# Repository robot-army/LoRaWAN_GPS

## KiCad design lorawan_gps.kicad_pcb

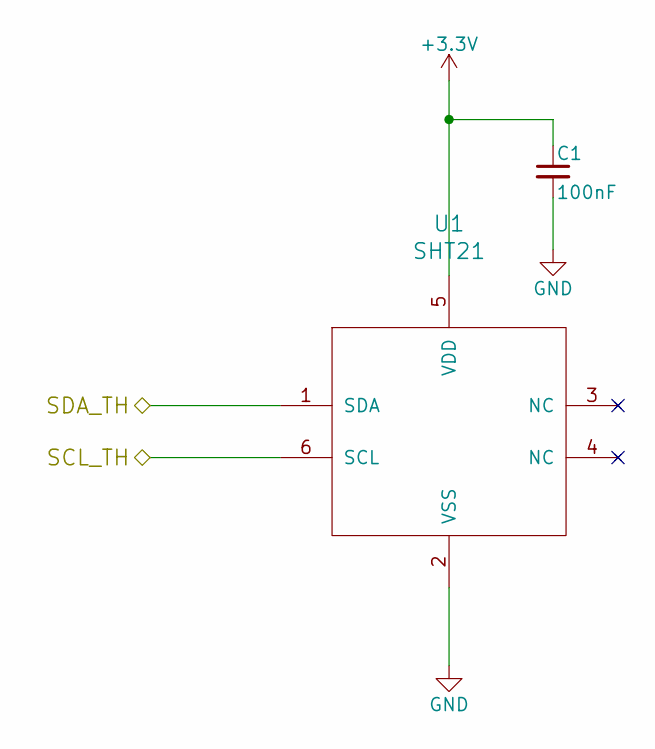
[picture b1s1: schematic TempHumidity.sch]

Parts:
C1: 100nF; C_0603
U1: SHT21

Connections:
/MCU/MPU_SCL: U1.6 (SCL); also elsewhere on the board
/MCU/MPU_SDA: U1.1 (SDA); also elsewhere on the board
GND: C1.2, U1.2 (VSS); also elsewhere on the board

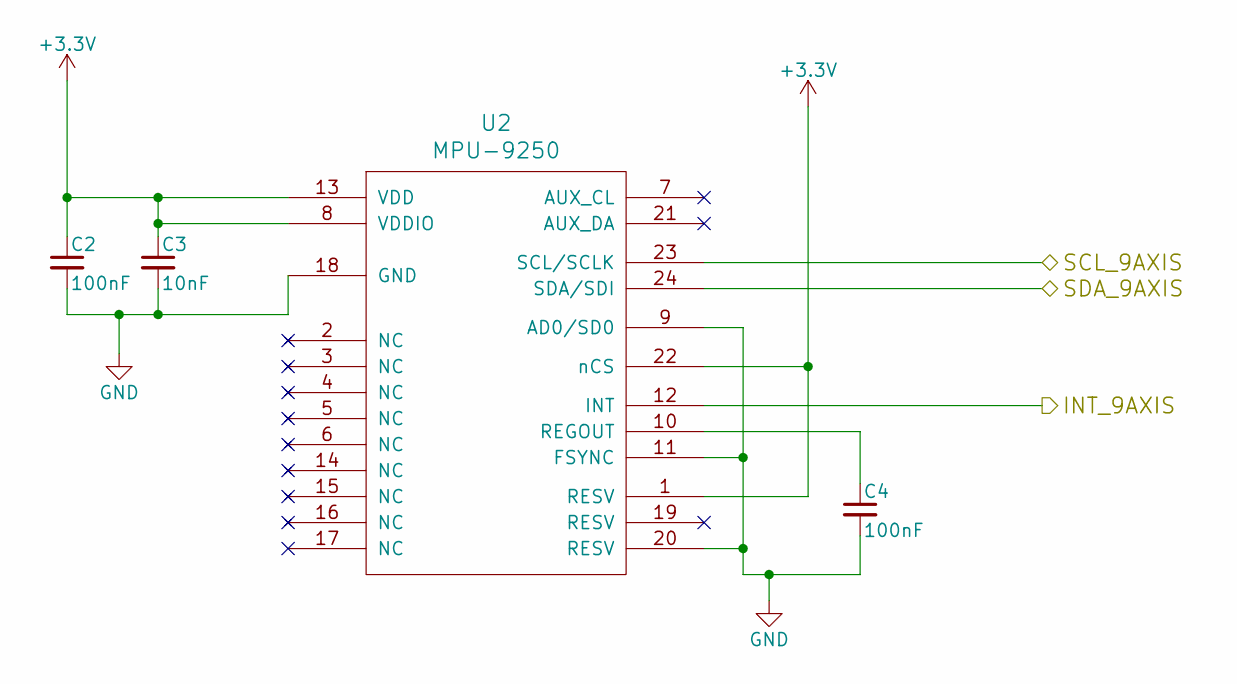
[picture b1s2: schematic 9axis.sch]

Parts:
C2, C4: 100nF; C_0603
C3: 10nF; C_0603
U2: MPU-9250; QFN-24-1EP_3x3mm_Pitch0.4mm

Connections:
/9axis/INT_9AXIS: U2.12 (INT); also elsewhere on the board
/MCU/MPU_SCL: U2.23 (SCL/SCLK); also elsewhere on the board
/MCU/MPU_SDA: U2.24 (SDA/SDI); also elsewhere on the board
GND: C2.2, C3.2, C4.2, U2.9 (AD0/SD0), U2.11 (FSYNC), U2.18 (GND), U2.20 (RESV); also elsewhere on the board
unnamed: C4.1, U2.10 (REGOUT)

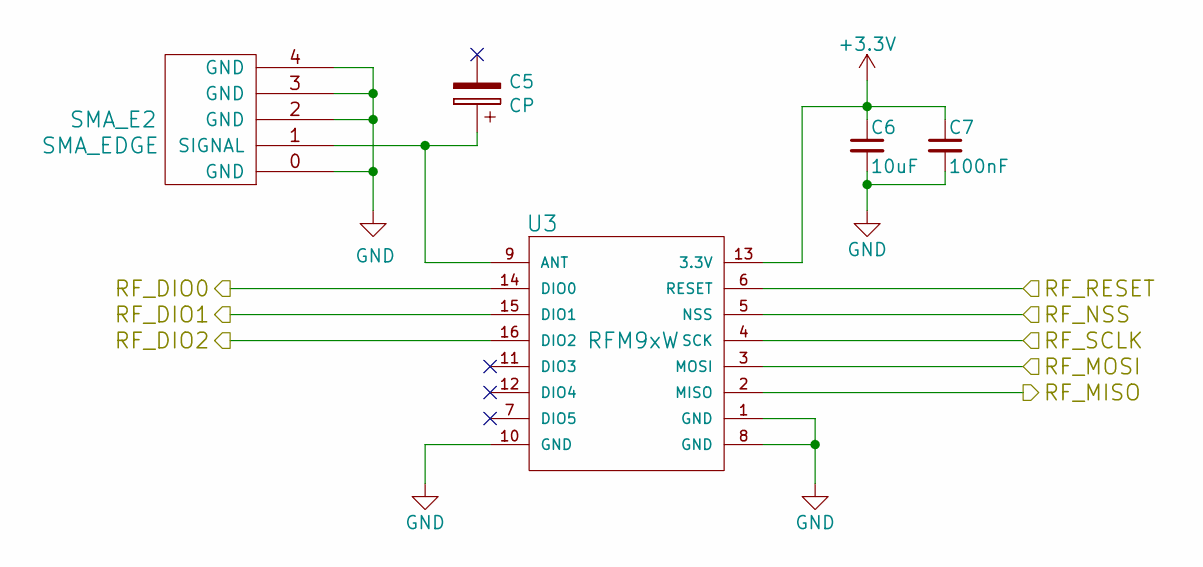
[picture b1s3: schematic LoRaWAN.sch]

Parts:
C5: CP; 0868AT43A0020; MFG Part Number 0868AT43A0020
C6: 10uF; C_0805
C7: 100nF; C_0603
SMA_E2: SMA_EDGE
U3: RFM9xW

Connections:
/MCU/MPU_D14: U3.6 (RESET); also elsewhere on the board
/MCU/MPU_IN14: U3.15 (DIO1); also elsewhere on the board
/MCU/MPU_INT5: U3.16 (DIO2); also elsewhere on the board
/MCU/MPU_INT9: U3.14 (DIO0); also elsewhere on the board
/MCU/MPU_MISO: U3.2 (MISO); also elsewhere on the board
/MCU/MPU_MOSI: U3.3 (MOSI); also elsewhere on the board
/MCU/MPU_SCK: U3.4 (SCK); also elsewhere on the board
/MCU/MPU_SS: U3.5 (NSS); also elsewhere on the board
GND: C6.2, C7.2, SMA_E2.0 (GND), SMA_E2.2 (GND), SMA_E2.3 (GND), SMA_E2.4 (GND), U3.1 (GND), U3.8 (GND), U3.10 (GND); also elsewhere on the board
unnamed: C5.1, SMA_E2.1 (SIGNAL), U3.9 (ANT)

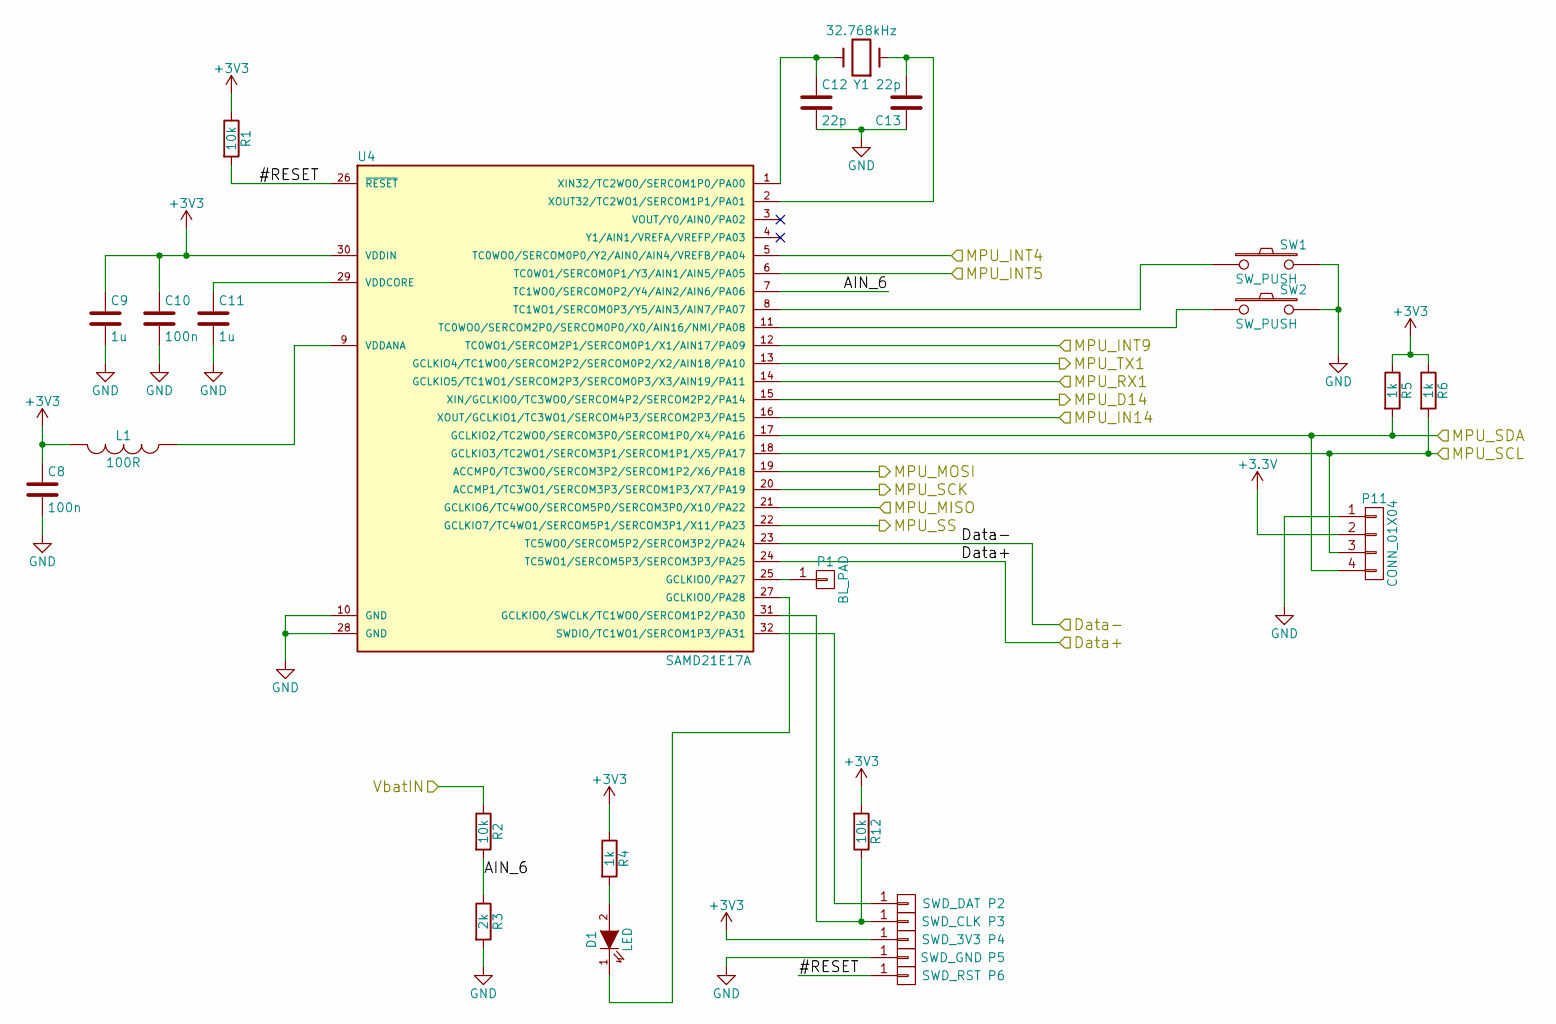
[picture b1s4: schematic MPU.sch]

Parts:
C8, C10: 100n; C_0603
C9, C11: 1u; C_0603
C12, C13: 22p; C_0603
D1: LED; C_0603
L1: 100R; C_0603
P1: BL_PAD; Measurement_Point_Round-TH_Small
P2: SWD_DAT; Measurement_Point_Round-TH_Small
P3: SWD_CLK; Measurement_Point_Round-TH_Small
P4: SWD_3V3; Measurement_Point_Round-TH_Small
P5: SWD_GND; Measurement_Point_Round-TH_Small
P6: SWD_RST; Measurement_Point_Round-TH_Small
P11: CONN_01X04; Pin_Header_Straight_1x04
R1, R2, R12: 10k; C_0603
R3: 2k; C_0603
R4, R5, R6: 1k; C_0603
SW1, SW2: SW_PUSH; SW_SPST_EVQP2
U4: SAMD21E17A; QFN-32-1EP_5x5mm_Pitch0.5mm
Y1: 32.768kHz; ABS07

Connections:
/9axis/INT_9AXIS: U4.5 (TC0WO0/SERCOM0P0/Y2/AIN0/AIN4/VREFB/PA04); also elsewhere on the board
/Battery and USB Connector/D+: U4.24 (TC5WO1/SERCOM5P3/SERCOM3P3/PA25); also elsewhere on the board
/Battery and USB Connector/D-: U4.23 (TC5WO0/SERCOM5P2/SERCOM3P2/PA24); also elsewhere on the board
/Battery and USB Connector/V_BAT: R2.1; also elsewhere on the board
/Battery and USB Connector/V_USB_Sense: U4.3 (VOUT/Y0/AIN0/PA02); also elsewhere on the board
/MCU/#RESET: P6.1, R1.2, U4.26 (~RESET~)
/MCU/AIN_6: R2.2, R3.1, U4.7 (TC1WO0/SERCOM0P2/Y4/AIN2/AIN6/PA06)
/MCU/MPU_D14: U4.15 (XIN/GCLKIO0/TC3WO0/SERCOM4P2/SERCOM2P2/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); also elsewhere on the board
/MCU/MPU_IN14: U4.16 (XOUT/GCLKIO1/TC3WO1/SERCOM4P3/SERCOM2P3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); also elsewhere on the board
/MCU/MPU_INT5: U4.6 (TC0W01/SERCOM0P1/Y3/AIN1/AIN5/PA05); also elsewhere on the board
/MCU/MPU_INT9: U4.12 (TC0WO1/SERCOM2P1/SERCOM0P1/X1/AIN17/PA09); also elsewhere on the board
/MCU/MPU_MISO: U4.21 (GCLKIO6/TC4WO0/SERCOM5P0/SERCOM3P0/X10/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); also elsewhere on the board
/MCU/MPU_MOSI: U4.19 (ACCMP0/TC3WO0/SERCOM3P2/SERCOM1P2/X6/PA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); also elsewhere on the board
/MCU/MPU_RX1: U4.14 (GCLKIO5/TC1WO1/SERCOM2P3/SERCOM0P3/X3/A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); also elsewhere on the board
/MCU/MPU_SCK: U4.20 (ACCMP1/TC3WO1/SERCOM3P3/SERCOM1P3/X7/PA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); also elsewhere on the board
/MCU/MPU_SCL: P11.3, R6.2, U4.18 (GCLKIO3/TC2WO1/SERCOM3P1/SERCOM1P1/X5/P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); also elsewhere on the board
/MCU/MPU_SDA: P11.4, R5.2, U4.17 (GCLKIO2/TC2WO0/SERCOM3P0/SERCOM1P0/X4/P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); also elsewhere on the board
/MCU/MPU_SS: U4.22 (GCLKIO7/TC4WO1/SERCOM5P1/SERCOM3P1/X11/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); also elsewhere on the board
/MCU/MPU_TX1: U4.13 (GCLKIO4/TC1WO0/SERCOM2P2/SERCOM0P2/X2/A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); also elsewhere on the board
GND: C8.2, C9.2, C10.2, C11.2, C12.2, C13.1, P5.1, P11.1, R3.2, SW1.2, SW2.2, U4.10 (GND), U4.28 (GND); also elsewhere on the board
unnamed: C11.1, U4.29 (VDDCORE)
unnamed: C12.1, U4.1 (XIN32/TC2WO0/SERCOM1P0/PA00), Y1.2
unnamed: C13.2, U4.2 (XOUT32/TC2WO1/SERCOM1P1/PA01), Y1.1
unnamed: D1.1 (K), U4.27 (GCLKIO0/PA28)
unnamed: D1.2 (A), R4.2
unnamed: L1.1, U4.9 (VDDANA)
unnamed: P1.1, U4.25 (GCLKIO0/PA27)
unnamed: P2.1, U4.32 (SWDIO/TC1WO1/SERCOM1P3/PA31)
unnamed: P3.1, R12.1, U4.31 (GCLKIO0/SWCLK/TC1WO0/SERCOM1P2/PA30)
unnamed: SW1.1, U4.8 (TC1WO1/SERCOM0P3/Y5/AIN3/AIN7/PA07)
unnamed: SW2.1, U4.11 (TC0WO0/SERCOM2P0/SERCOM0P0/X0/AIN16/NMI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)

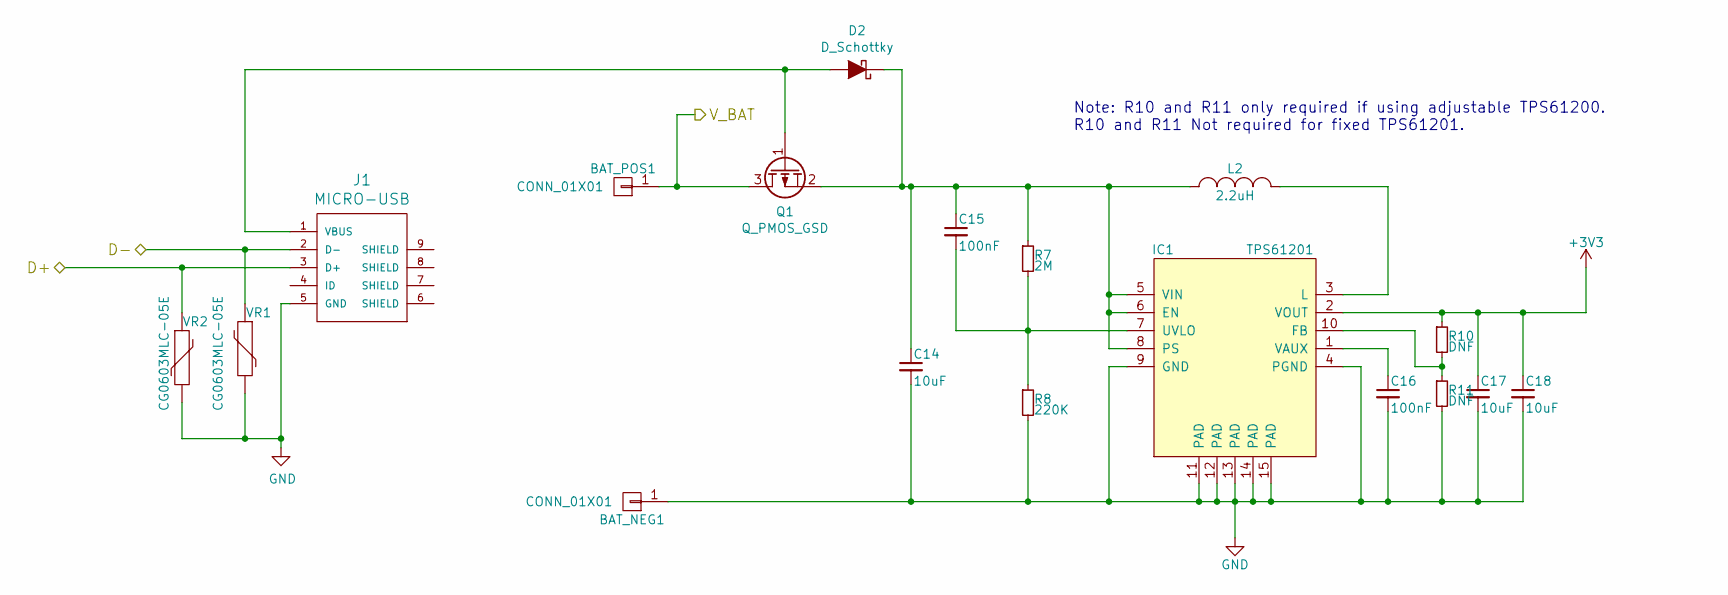
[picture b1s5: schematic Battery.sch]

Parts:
BAT_NEG1: CONN_01X01; Measurement_Point_Round-TH_Small
BAT_POS1: CONN_01X01; Measurement_Point_Round-TH_Small
C14, C17, C18: 10uF; C_0805
C15, C16: 100nF; C_0603
D2: D_Schottky; SOD-323; MFG Part Number MSS1P2L
IC1: TPS61201; VSON-10-1(4)EP_3x3mm_Pitch0.5mm
J1: MICRO-USB
L2: 2.2uH; Neosid_Inductor_SMS-ME3015
Q1: Q_PMOS_GSD; SOT-23; MFG Part Number FDN340P
R7: 2M; C_0603
R8: 220K; C_0603
R10, R11: DNF; C_0603
VR1, VR2: CG0603MLC-05E; C_0603

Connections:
/Battery and USB Connector/D+: J1.3 (D+), VR2.1; also elsewhere on the board
/Battery and USB Connector/D-: J1.2 (D-), VR1.1; also elsewhere on the board
/Battery and USB Connector/V_BAT: BAT_POS1.1, Q1.3 (D); also elsewhere on the board
GND: BAT_NEG1.1, C14.2, C16.2, C17.2, C18.2, IC1.4 (PGND), IC1.9 (GND), IC1.11 (PAD), IC1.12 (PAD), IC1.13 (PAD), IC1.14 (PAD), IC1.15 (PAD), J1.5 (GND), R8.2, R11.2, VR1.2, VR2.2; also elsewhere on the board
unnamed: C14.1, C15.1, D2.1 (K), IC1.5 (VIN), IC1.6 (EN), IC1.8 (PS), L2.1, Q1.2 (S), R7.1
unnamed: C15.2, IC1.7 (UVLO), R7.2, R8.1
unnamed: C16.1, IC1.1 (VAUX)
unnamed 32: D2.2 (A), J1.1 (VBUS), Q1.1 (G); also elsewhere on the board
unnamed: IC1.3 (L), L2.2
unnamed: IC1.10 (FB), R10.2, R11.1

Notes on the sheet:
Note: R10 and R11 only required if using adjustable TPS61200. R10 and R11 Not required for fixed TPS61201.

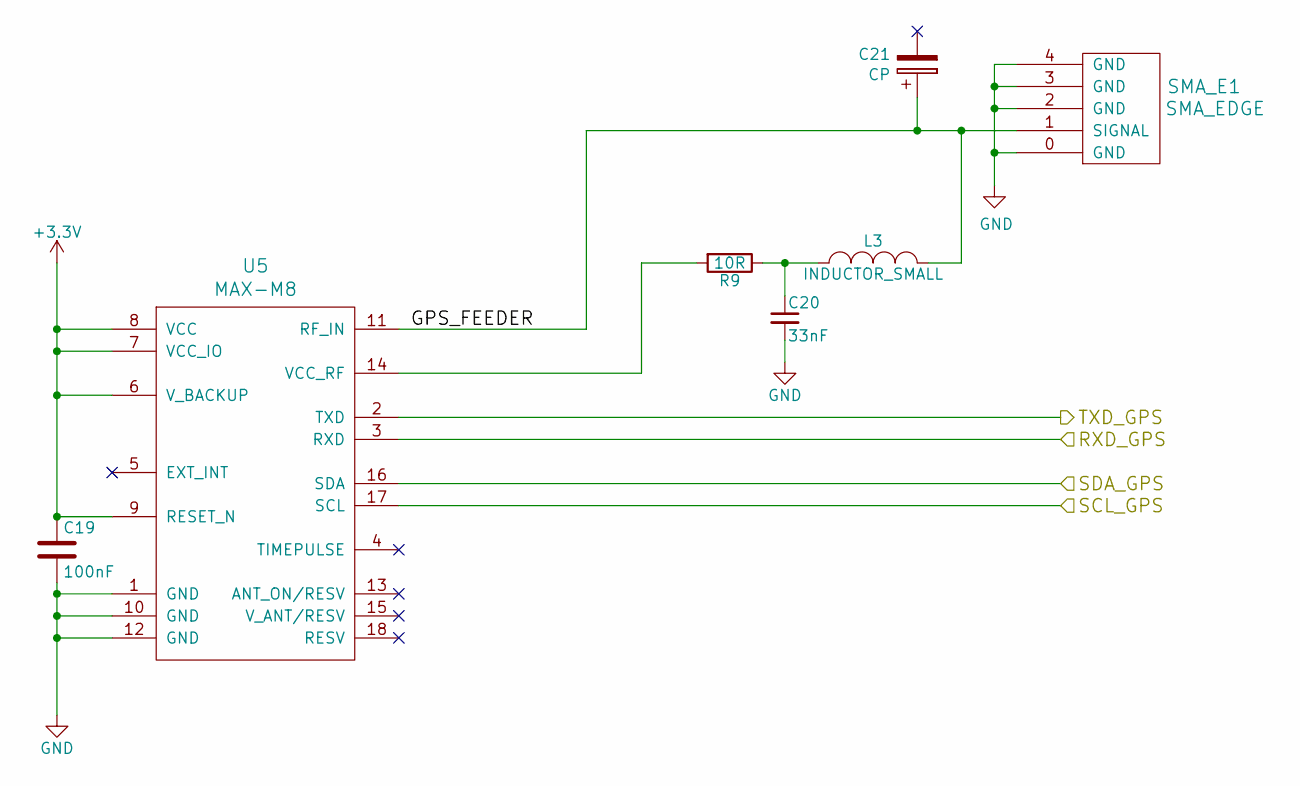
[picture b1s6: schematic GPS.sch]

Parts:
C19: 100nF; C_0603
C20: 33nF; C_0603
C21: CP; 1575AT43A0040
L3: INDUCTOR_SMALL; C_0603
R9: 10R; C_0603
SMA_E1: SMA_EDGE
U5: MAX-M8

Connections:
/GPS/GPS_FEEDER: C21.1, L3.2, SMA_E1.1 (SIGNAL), U5.11 (RF_IN)
/MCU/MPU_RX1: U5.2 (TXD); also elsewhere on the board
/MCU/MPU_SCL: U5.17 (SCL); also elsewhere on the board
/MCU/MPU_SDA: U5.16 (SDA); also elsewhere on the board
/MCU/MPU_TX1: U5.3 (RXD); also elsewhere on the board
GND: C19.2, C20.2, SMA_E1.0 (GND), SMA_E1.2 (GND), SMA_E1.3 (GND), SMA_E1.4 (GND), U5.1 (GND), U5.10 (GND), U5.12 (GND); also elsewhere on the board
unnamed: C20.1, L3.1, R9.1
unnamed: R9.2, U5.14 (VCC_RF)

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
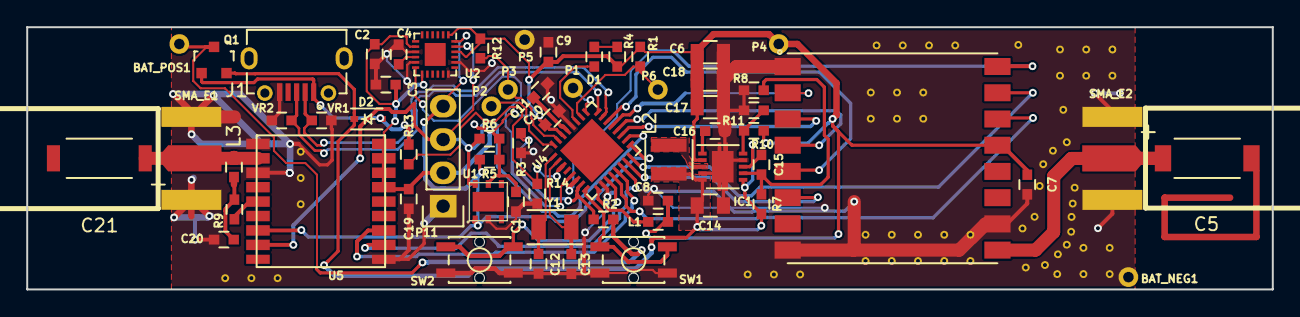
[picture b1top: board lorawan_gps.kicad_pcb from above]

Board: 2 copper layers, 95.0 x 20.0 mm, 64 parts (0 on the bottom side), 43 nets.

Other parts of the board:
R13, R14: R; C_0603

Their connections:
/Battery and USB Connector/V_USB_Sense: R13.2, R14.1; also elsewhere on the board
GND: R14.2; also elsewhere on the board
unnamed 32: R13.1; also elsewhere on the board

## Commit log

2016-03-06 Fixed library association for MPU-9250
2016-03-06 Added SAMD21 processor and associated bits from other project
2016-03-06 Added outline for AAA battery size
2016-03-24 started layout, completed schematic
2016-03-25 All connected
2016-03-25 Added edge-mount SMAs
2016-03-25 Added Edge-mount SMA connectors to layout - NOTE: 1 UNCONNECT
2016-03-28 moved battery input and fixed dodgy ground plane
2016-03-28 Changed L3 to 0603, L2 to 3x3, Fixed P8 silk and made gerbers
2016-04-03 Started changes after first round, micro usb connector, fixing footprint for accelerometer
2016-04-19 Started work to add the power mux and USB connector
2016-05-09 Added USB connector, diode or etc to layout@
2016-05-09 Fixed track near edge by accelerometer
2016-05-09 Added dielectric antennae, finished wiring, DRC pass, no unconnects
2016-05-11 Added USB monitoring resistors, still need to set values. Also added stitching vias and tried to clean up some layout
2016-05-12 Fixed layout, updated RF track width, switch footprint fixed, layout around accelerometer fixed
2016-05-12 Fixed up silkscreen
2016-05-12 Fixed up silkscreen some more
2016-05-12 Added BOM, new gerbers
2016-05-12 Fixed single bad unconnect
